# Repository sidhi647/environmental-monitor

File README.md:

# environmental-monitor
Version 1:
ESP32 collects environmental data
BME280 measures temperature, humidity, and pressure
OLED displays real-time measurements
Custom PCB designed in KiCad

SD-card data logging tested but not completed - SD card module is not connecting

Case Study: https://docs.google.com/document/d/11CGSjNDkG4XqaT4TrCSuE653sdD-C-xeLsDyoSSBAY4/edit?usp=sharing

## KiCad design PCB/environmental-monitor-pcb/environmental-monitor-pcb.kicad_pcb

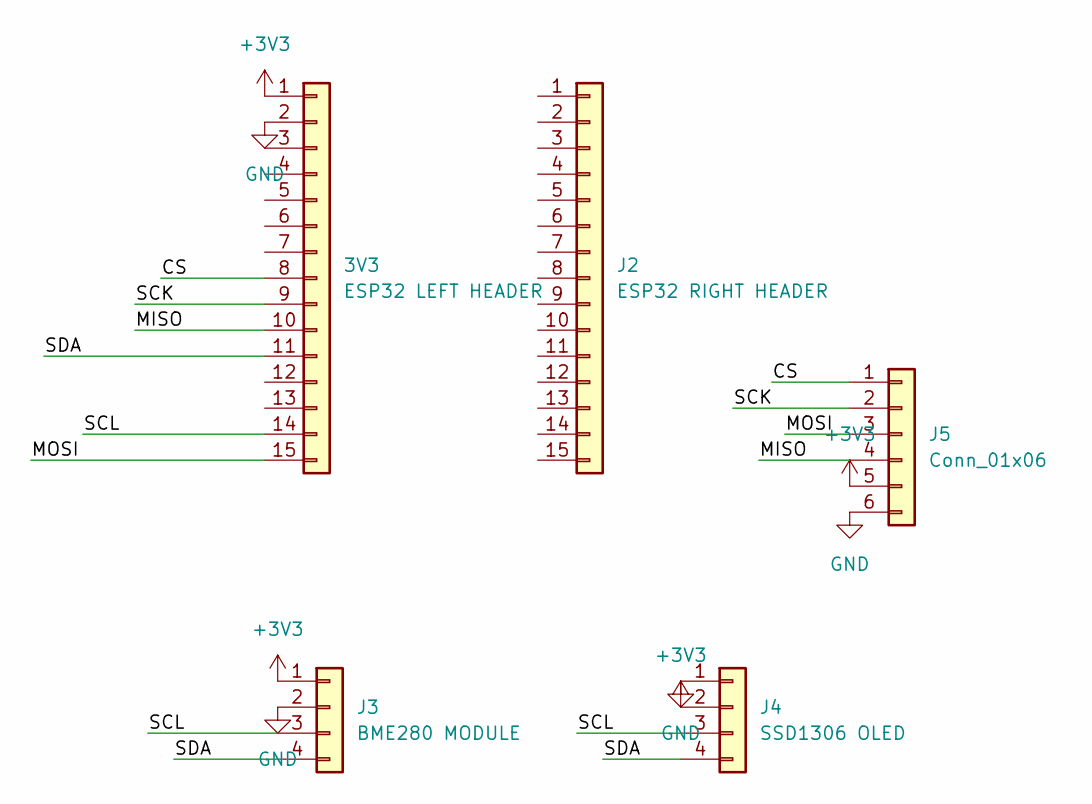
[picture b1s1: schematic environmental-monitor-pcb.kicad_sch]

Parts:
3V3: ESP32 LEFT HEADER; PinHeader_1x15_P2.54mm_Vertical
J2: ESP32 RIGHT HEADER; PinHeader_1x15_P2.54mm_Vertical
J3: BME280 MODULE; PinHeader_1x04_P2.54mm_Vertical
J4: SSD1306 OLED; PinHeader_1x04_P2.54mm_Vertical
J5: Conn_01x06; PinHeader_1x06_P2.54mm_Vertical

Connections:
+3V3: 3V3.1, J3.1, J4.2, J5.5
/CS: 3V3.8, J5.1
/MISO: 3V3.10, J5.4
/MOSI: 3V3.15, J5.3
/SCK: 3V3.9, J5.2
/SCL: 3V3.14, J3.3, J4.3
/SDA: 3V3.11, J3.4, J4.4
GND: 3V3.2, J3.2, J4.1, J5.6

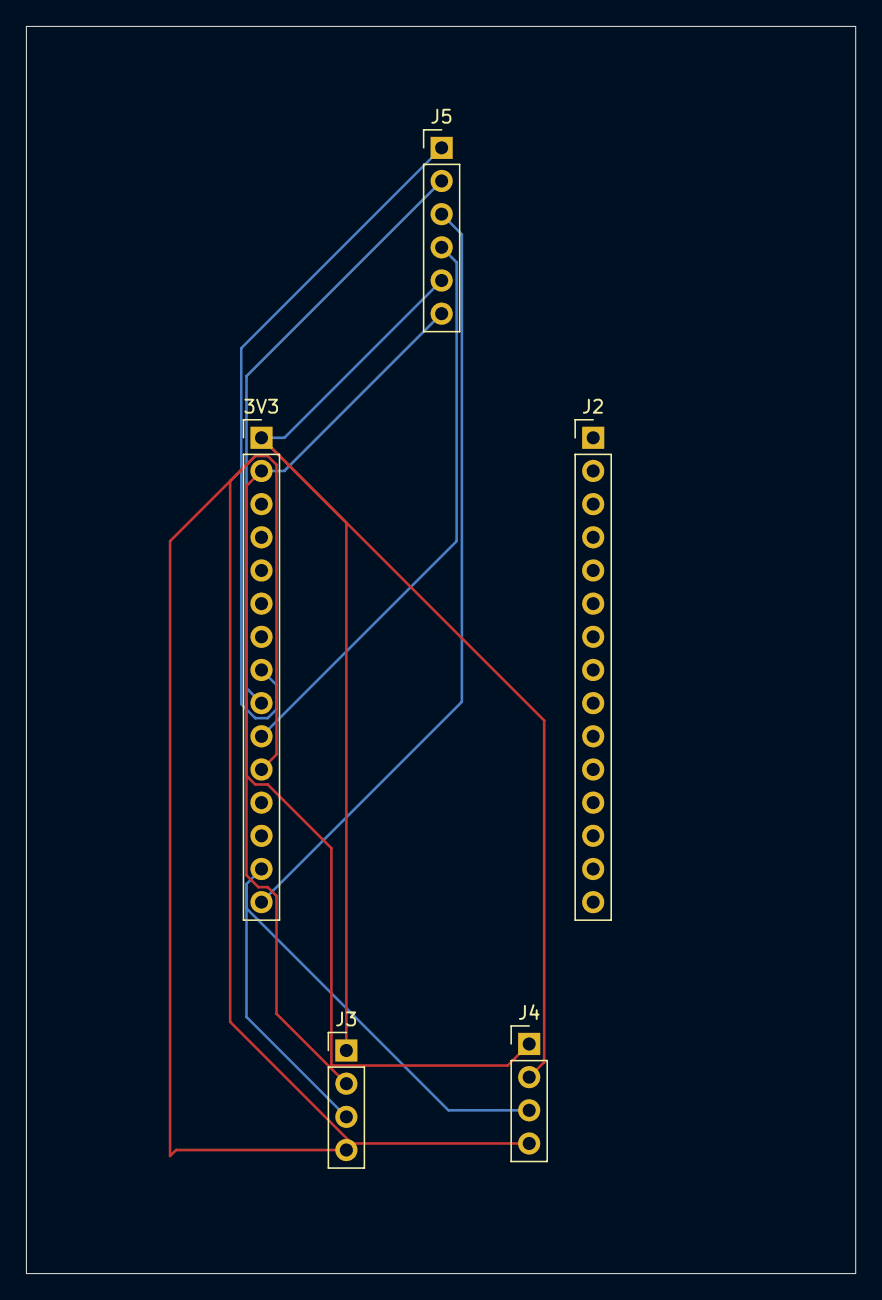
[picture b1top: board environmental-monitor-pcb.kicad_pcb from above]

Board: 2 copper layers, 63.5 x 95.5 mm, 5 parts (0 on the bottom side), 8 nets.
